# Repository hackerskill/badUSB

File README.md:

# badUSB
A CH552G powered BadUSB keystroke injection tool that emulates a standard USB keyboard to execute automated payloads.

### A compact usb stick style badUSB based on CH552G.
---
USB stick style device to emulate a keyboard for automating payload execution.

## Features
- CH552G acts as the main microcontroller
- Fast injection speed
- USB A connectivity
- LEDs for visual status and feedback
- Compact USB stick style PCB

---

# Schematics-

# PCB-

## How It Works

1. CH552G emulates a standard keyboard.

2. Depending on code, it either waits for bottom button input or automatically injects the payload coded in it.

3. The upper button in pressed while plugging in to enter programming mode.

# BOM-
| Component Name | Description | Quantity |
| :--- | :--- | :---: |
| **CH552G** | Chipset | 1 |
| **Resistors** | Resistors for Led| 4 |
| **Capacitors** | Capacitors for decoupling | 2 |
| **Leds** | Led for showing status | 3 |
| **Buttons** | Buttons for mode switching | 2 |
| **Custom PCB** | Custom PCB | 1 |

---

**Made by hackerskill**

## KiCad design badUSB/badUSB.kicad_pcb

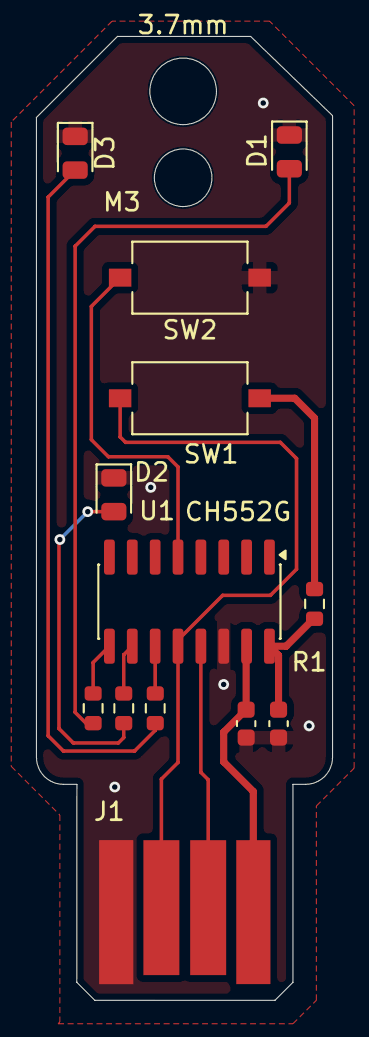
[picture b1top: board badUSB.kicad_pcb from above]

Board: 2 copper layers, 16.5 x 53.5 mm, 15 parts (0 on the bottom side), 13 nets.

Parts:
3.7mm: 3.7mm; MountingHole_3.7mm
C1, C2: 100nF; C_0603_1608Metric
D1, D2, D3: LED; LED_0805_2012Metric
J1: USB_A; USB-A
M3: MountingHole_3.2mm_M3
R1: 10k; R_0603_1608Metric
R2, R3, R4: 330R; R_0603_1608Metric
SW1, SW2: SW_Push; SW_Tactile_SPST_NO_Straight_CK_PTS636Sx25SMTRLFS
U1: CH552G; SOIC-16_3.9x9.9mm_P1.27mm

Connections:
+3V3: C2.2, R1.1, U1.16 (3V3)
/D+: J1.3 (D+), SW1.1, U1.12 (P3.6)
/D-: J1.2 (D-), U1.13 (P3.7)
/P1.1: R2.1, U1.9 (P1.1)
/P1.7: SW2.1, U1.5 (P1.7)
/P3.2: R3.1, U1.10 (P3.3)
/P3.4: R4.1, U1.11 (P3.4)
GND: C1.2, C2.1, D1.1 (K), D2.1 (K), D3.1 (K), J1.4 (GND), SW2.2, U1.14 (GND)
unnamed: D1.2 (A), R2.2
unnamed: D2.2 (A), R3.2
unnamed: D3.2 (A), R4.2
unnamed: R1.2, SW1.2
VBUS: C1.1, J1.1 (VBUS), U1.15 (VCC)
